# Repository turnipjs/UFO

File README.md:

# UFO

This is the Unified Full-size Ortholinear keyboard, or UFO for short. It has 114 keys in 6 rows and 19 columns, per key RGB, and N-Key roll over. It is built around a Raspberry Pi Pico and has a doodle of a UFO abducting a spherical cow in a vacuum.

# BOM
1x Main PCB  
1x Bottom Case PCB  
1x Top Plate PCB  
1x Raspberry Pi Pico  
114x Kailh style hot swap sockets for MX style switches  
114x SK6812-MINI-E RGB LEDs  
114x 1N4148W or other similar SOD-123 diodes  
Solder, Solder Paste, Flux as needed  
8x M2 threaded 3mm diameter 8mm long standoffs  
8x M2 threaded 5mm long screws  

# Firmware
The firmware will be available as the UFO keyboard in QMK repository. It is also available in [my personal QMK repository](https://github.com/turnipjs/qmk_firmware).

# Images

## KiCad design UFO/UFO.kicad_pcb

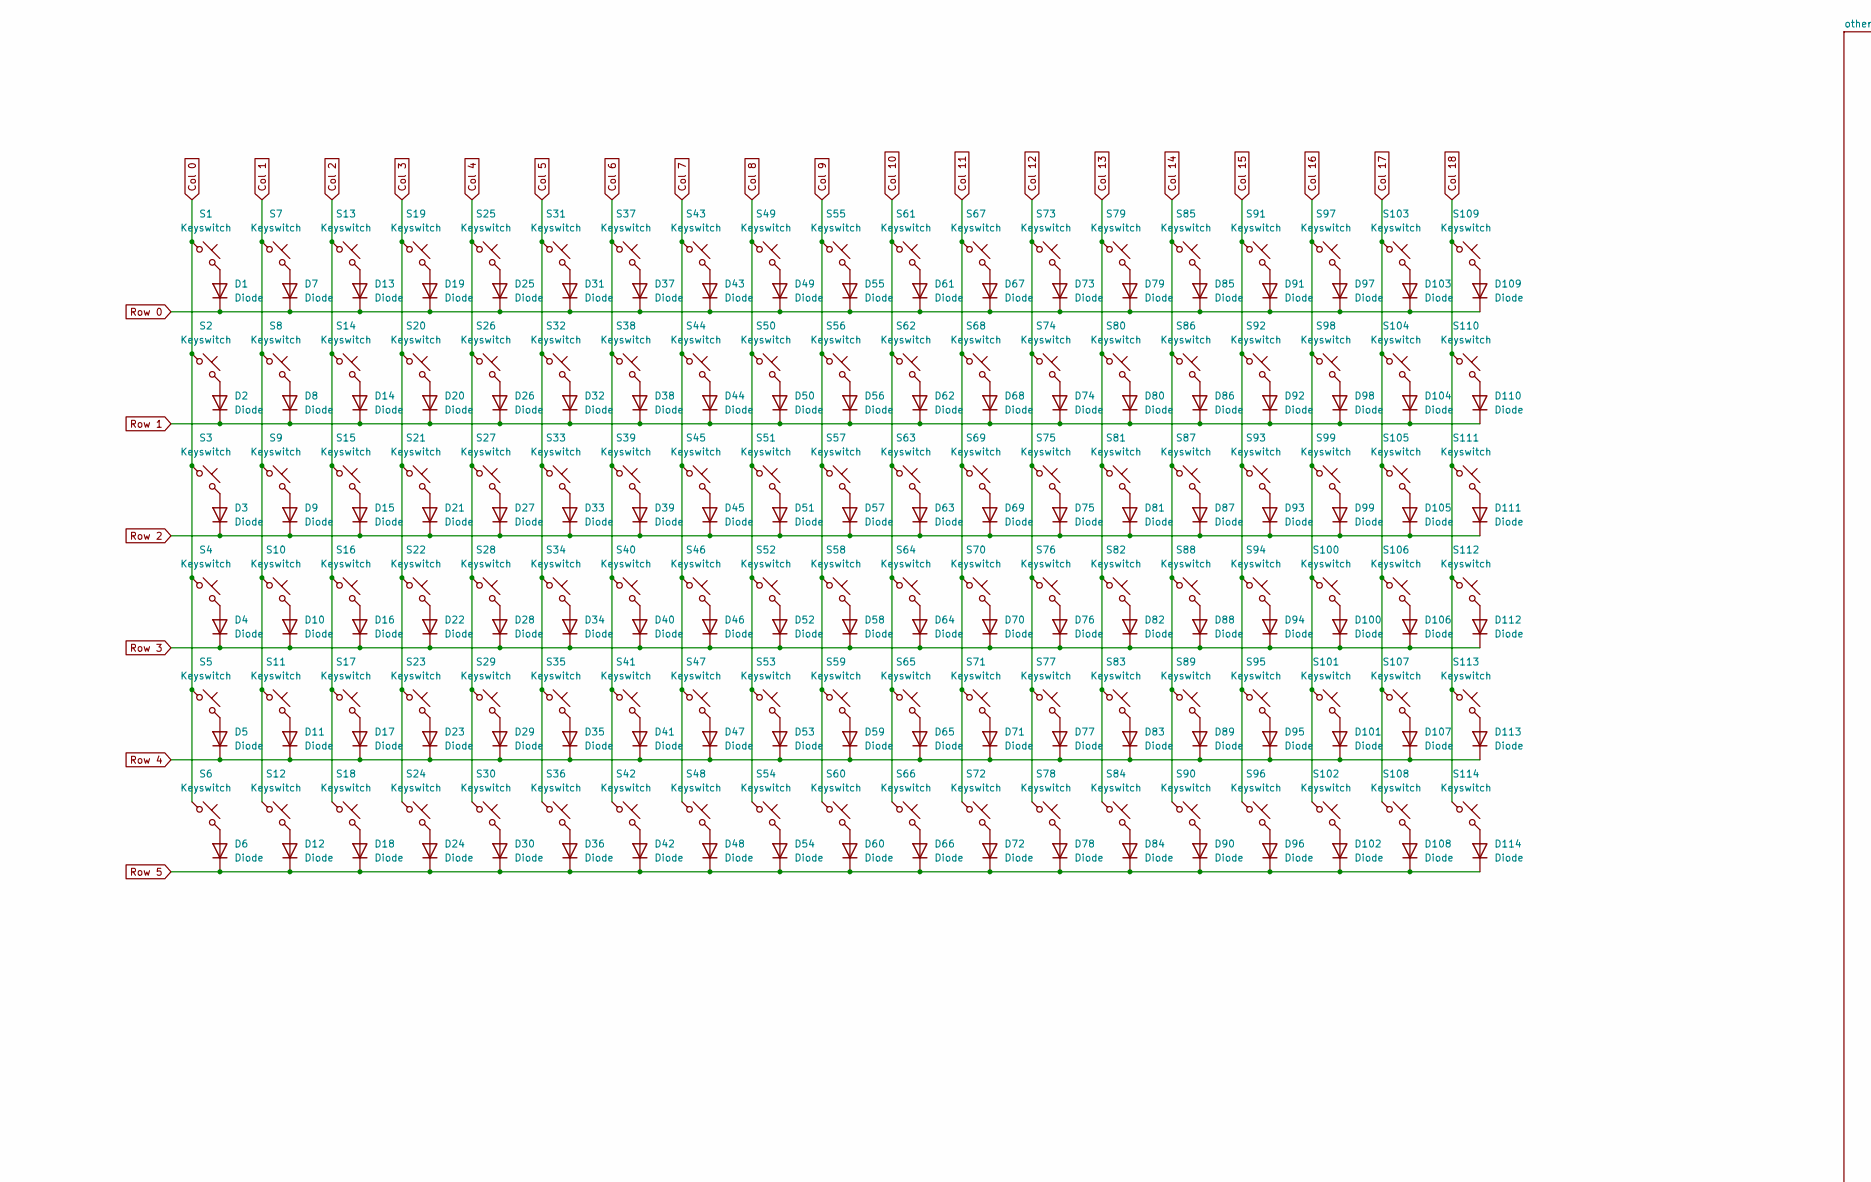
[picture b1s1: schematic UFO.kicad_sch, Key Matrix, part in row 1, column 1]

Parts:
D1, D2, D3, D4, D5, D6, D7, D8, D9, D10, D11, D12, D13, D14, D15, D16, D17, D18, D19, D20, D21, D22, D23, D24, D25, D26, D27, D28, D29, D30, D31, D32, D33, D34, D35, D36, D37, D38, D39, D40, D41, D42, D43, D44, D45, D46, D47, D48, D49, D50, D51, D52, D53, D54, D55, D56, D57, D58, D59, D60, D61, D62, D63, D64, D65, D66, D67, D68, D69, D70, D71, D72, D73, D74, D75, D76, D77, D78, D79, D80, D81, D82, D83, D84, D85, D86, D87, D88, D89, D90, D91, D92, D93, D94, D95, D96, D97, D98, D99, D100, D101, D102, D103, D104, D105, D106, D107, D108, D109, D110, D111, D112, D113, D114: Diode; Diode_SOD-123
S1, S2, S3, S4, S5, S6, S7, S8, S9, S10, S11, S12, S13, S14, S15, S16, S17, S18, S19, S20, S21, S22, S23, S24, S25, S26, S27, S28, S29, S30, S31, S32, S33, S34, S35, S36, S37, S38, S39, S40, S41, S42, S43, S44, S45, S46, S47, S48, S49, S50, S51, S52, S53, S54, S55, S56, S57, S58, S59, S60, S61, S62, S63, S64, S65, S66, S67, S68, S69, S70, S71, S72, S73, S74, S75, S76, S77, S78, S79, S80, S81, S82, S83, S84, S85, S86, S87, S88, S89, S90, S91, S92, S93, S94, S95, S96, S97, S98, S99, S100, S101, S102, S103, S104, S105, S106, S107, S108, S109, S110, S111, S112, S113, S114: Keyswitch; Hotswap_MX_1.00u

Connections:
Col 0: S1.1, S2.1, S3.1, S4.1, S5.1, S6.1; also elsewhere on the board
Col 1: S7.1, S8.1, S9.1, S10.1, S11.1, S12.1; also elsewhere on the board
Col 2: S13.1, S14.1, S15.1, S16.1, S17.1, S18.1; also elsewhere on the board
Col 3: S19.1, S20.1, S21.1, S22.1, S23.1, S24.1; also elsewhere on the board
Col 4: S25.1, S26.1, S27.1, S28.1, S29.1, S30.1; also elsewhere on the board
Col 5: S31.1, S32.1, S33.1, S34.1, S35.1, S36.1; also elsewhere on the board
Col 6: S37.1, S38.1, S39.1, S40.1, S41.1, S42.1; also elsewhere on the board
Col 7: S43.1, S44.1, S45.1, S46.1, S47.1, S48.1; also elsewhere on the board
Col 8: S49.1, S50.1, S51.1, S52.1, S53.1, S54.1; also elsewhere on the board
Col 9: S55.1, S56.1, S57.1, S58.1, S59.1, S60.1; also elsewhere on the board
Col 10: S61.1, S62.1, S63.1, S64.1, S65.1, S66.1; also elsewhere on the board
Col 11: S67.1, S68.1, S69.1, S70.1, S71.1, S72.1; also elsewhere on the board
Col 12: S73.1, S74.1, S75.1, S76.1, S77.1, S78.1; also elsewhere on the board
Col 13: S79.1, S80.1, S81.1, S82.1, S83.1, S84.1; also elsewhere on the board
Col 14: S85.1, S86.1, S87.1, S88.1, S89.1, S90.1; also elsewhere on the board
Col 15: S91.1, S92.1, S93.1, S94.1, S95.1, S96.1; also elsewhere on the board
Col 16: S97.1, S98.1, S99.1, S100.1, S101.1, S102.1; also elsewhere on the board
Col 17: S103.1, S104.1, S105.1, S106.1, S107.1, S108.1; also elsewhere on the board
Col 18: S109.1, S110.1, S111.1, S112.1, S113.1, S114.1; also elsewhere on the board
unnamed: D1.2 (A), S1.2
unnamed: D2.2 (A), S2.2
unnamed: D3.2 (A), S3.2
unnamed: D4.2 (A), S4.2
unnamed: D5.2 (A), S5.2
unnamed: D6.2 (A), S6.2
unnamed: D7.2 (A), S7.2
unnamed: D8.2 (A), S8.2
unnamed: D9.2 (A), S9.2
unnamed: D10.2 (A), S10.2
unnamed: D11.2 (A), S11.2
unnamed: D12.2 (A), S12.2
unnamed: D13.2 (A), S13.2
unnamed: D14.2 (A), S14.2
unnamed: D15.2 (A), S15.2
unnamed: D16.2 (A), S16.2
unnamed: D17.2 (A), S17.2
unnamed: D18.2 (A), S18.2
unnamed: D19.2 (A), S19.2
unnamed: D20.2 (A), S20.2
unnamed: D21.2 (A), S21.2
unnamed: D22.2 (A), S22.2
unnamed: D23.2 (A), S23.2
unnamed: D24.2 (A), S24.2
unnamed: D25.2 (A), S25.2
unnamed: D26.2 (A), S26.2
unnamed: D27.2 (A), S27.2
unnamed: D28.2 (A), S28.2
unnamed: D29.2 (A), S29.2
unnamed: D30.2 (A), S30.2
unnamed: D31.2 (A), S31.2
unnamed: D32.2 (A), S32.2
unnamed: D33.2 (A), S33.2
unnamed: D34.2 (A), S34.2
unnamed: D35.2 (A), S35.2
unnamed: D36.2 (A), S36.2
unnamed: D37.2 (A), S37.2
unnamed: D38.2 (A), S38.2
unnamed: D39.2 (A), S39.2
unnamed: D40.2 (A), S40.2
unnamed: D41.2 (A), S41.2
unnamed: D42.2 (A), S42.2
unnamed: D43.2 (A), S43.2
unnamed: D44.2 (A), S44.2
unnamed: D45.2 (A), S45.2
unnamed: D46.2 (A), S46.2
unnamed: D47.2 (A), S47.2
unnamed: D48.2 (A), S48.2
unnamed: D49.2 (A), S49.2
unnamed: D50.2 (A), S50.2
unnamed: D51.2 (A), S51.2
unnamed: D52.2 (A), S52.2
unnamed: D53.2 (A), S53.2
unnamed: D54.2 (A), S54.2
unnamed: D55.2 (A), S55.2
unnamed: D56.2 (A), S56.2
unnamed: D57.2 (A), S57.2
unnamed: D58.2 (A), S58.2
unnamed: D59.2 (A), S59.2
unnamed: D60.2 (A), S60.2
unnamed: D61.2 (A), S61.2
unnamed: D62.2 (A), S62.2
unnamed: D63.2 (A), S63.2
unnamed: D64.2 (A), S64.2
unnamed: D65.2 (A), S65.2
unnamed: D66.2 (A), S66.2
unnamed: D67.2 (A), S67.2
unnamed: D68.2 (A), S68.2
unnamed: D69.2 (A), S69.2
unnamed: D70.2 (A), S70.2
unnamed: D71.2 (A), S71.2
unnamed: D72.2 (A), S72.2
unnamed: D73.2 (A), S73.2
unnamed: D74.2 (A), S74.2
unnamed: D75.2 (A), S75.2
unnamed: D76.2 (A), S76.2
unnamed: D77.2 (A), S77.2
unnamed: D78.2 (A), S78.2
unnamed: D79.2 (A), S79.2
unnamed: D80.2 (A), S80.2
unnamed: D81.2 (A), S81.2
unnamed: D82.2 (A), S82.2
unnamed: D83.2 (A), S83.2
unnamed: D84.2 (A), S84.2
unnamed: D85.2 (A), S85.2
unnamed: D86.2 (A), S86.2
unnamed: D87.2 (A), S87.2
unnamed: D88.2 (A), S88.2
unnamed: D89.2 (A), S89.2
unnamed: D90.2 (A), S90.2
unnamed: D91.2 (A), S91.2
unnamed: D92.2 (A), S92.2
unnamed: D93.2 (A), S93.2
unnamed: D94.2 (A), S94.2
unnamed: D95.2 (A), S95.2
unnamed: D96.2 (A), S96.2
unnamed: D97.2 (A), S97.2
unnamed: D98.2 (A), S98.2
unnamed: D99.2 (A), S99.2
unnamed: D100.2 (A), S100.2
unnamed: D101.2 (A), S101.2
unnamed: D102.2 (A), S102.2
unnamed: D103.2 (A), S103.2
unnamed: D104.2 (A), S104.2
unnamed: D105.2 (A), S105.2
unnamed: D106.2 (A), S106.2
unnamed: D107.2 (A), S107.2
unnamed: D108.2 (A), S108.2
unnamed: D109.2 (A), S109.2
unnamed: D110.2 (A), S110.2
unnamed: D111.2 (A), S111.2
unnamed: D112.2 (A), S112.2
unnamed: D113.2 (A), S113.2
unnamed: D114.2 (A), S114.2
Row 0: D1.1 (K), D7.1 (K), D13.1 (K), D19.1 (K), D25.1 (K), D31.1 (K), D37.1 (K), D43.1 (K), D49.1 (K), D55.1 (K), D61.1 (K), D67.1 (K), D73.1 (K), D79.1 (K), D85.1 (K), D91.1 (K), D97.1 (K), D103.1 (K), D109.1 (K); also elsewhere on the board
Row 1: D2.1 (K), D8.1 (K), D14.1 (K), D20.1 (K), D26.1 (K), D32.1 (K), D38.1 (K), D44.1 (K), D50.1 (K), D56.1 (K), D62.1 (K), D68.1 (K), D74.1 (K), D80.1 (K), D86.1 (K), D92.1 (K), D98.1 (K), D104.1 (K), D110.1 (K); also elsewhere on the board
Row 2: D3.1 (K), D9.1 (K), D15.1 (K), D21.1 (K), D27.1 (K), D33.1 (K), D39.1 (K), D45.1 (K), D51.1 (K), D57.1 (K), D63.1 (K), D69.1 (K), D75.1 (K), D81.1 (K), D87.1 (K), D93.1 (K), D99.1 (K), D105.1 (K), D111.1 (K); also elsewhere on the board
Row 3: D4.1 (K), D10.1 (K), D16.1 (K), D22.1 (K), D28.1 (K), D34.1 (K), D40.1 (K), D46.1 (K), D52.1 (K), D58.1 (K), D64.1 (K), D70.1 (K), D76.1 (K), D82.1 (K), D88.1 (K), D94.1 (K), D100.1 (K), D106.1 (K), D112.1 (K); also elsewhere on the board
Row 4: D5.1 (K), D11.1 (K), D17.1 (K), D23.1 (K), D29.1 (K), D35.1 (K), D41.1 (K), D47.1 (K), D53.1 (K), D59.1 (K), D65.1 (K), D71.1 (K), D77.1 (K), D83.1 (K), D89.1 (K), D95.1 (K), D101.1 (K), D107.1 (K), D113.1 (K); also elsewhere on the board
Row 5: D6.1 (K), D12.1 (K), D18.1 (K), D24.1 (K), D30.1 (K), D36.1 (K), D42.1 (K), D48.1 (K), D54.1 (K), D60.1 (K), D66.1 (K), D72.1 (K), D78.1 (K), D84.1 (K), D90.1 (K), D96.1 (K), D102.1 (K), D108.1 (K), D114.1 (K); also elsewhere on the board

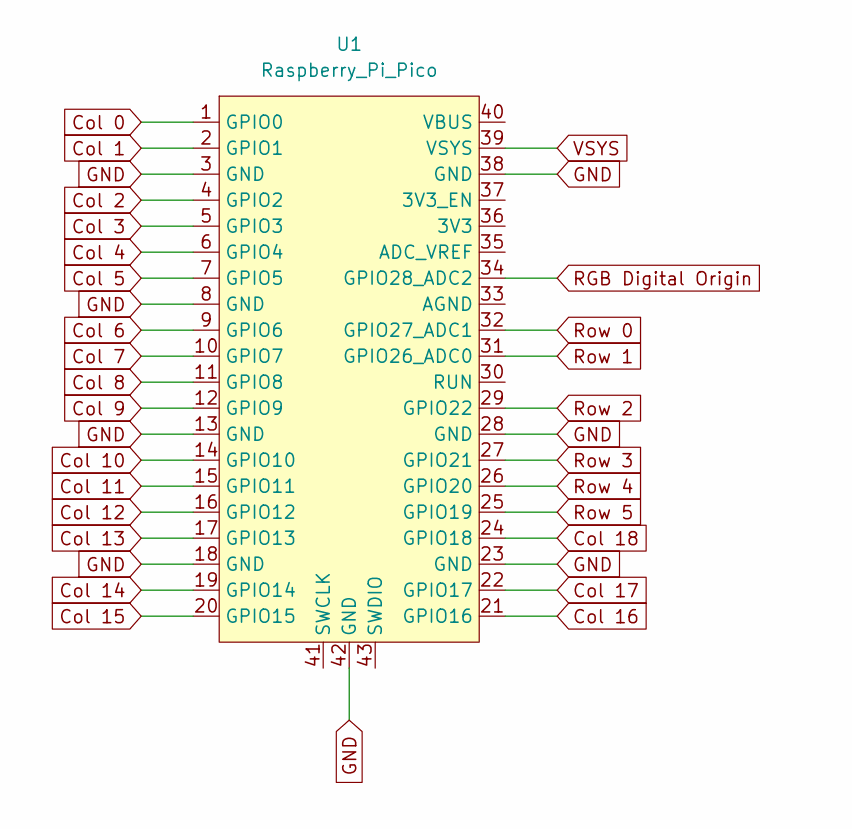
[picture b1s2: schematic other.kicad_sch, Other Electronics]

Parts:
U1: Raspberry_Pi_Pico

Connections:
Col 0: U1.1 (GPIO0); also elsewhere on the board
Col 1: U1.2 (GPIO1); also elsewhere on the board
Col 2: U1.4 (GPIO2); also elsewhere on the board
Col 3: U1.5 (GPIO3); also elsewhere on the board
Col 4: U1.6 (GPIO4); also elsewhere on the board
Col 5: U1.7 (GPIO5); also elsewhere on the board
Col 6: U1.9 (GPIO6); also elsewhere on the board
Col 7: U1.10 (GPIO7); also elsewhere on the board
Col 8: U1.11 (GPIO8); also elsewhere on the board
Col 9: U1.12 (GPIO9); also elsewhere on the board
Col 10: U1.14 (GPIO10); also elsewhere on the board
Col 11: U1.15 (GPIO11); also elsewhere on the board
Col 12: U1.16 (GPIO12); also elsewhere on the board
Col 13: U1.17 (GPIO13); also elsewhere on the board
Col 14: U1.19 (GPIO14); also elsewhere on the board
Col 15: U1.20 (GPIO15); also elsewhere on the board
Col 16: U1.21 (GPIO16); also elsewhere on the board
Col 17: U1.22 (GPIO17); also elsewhere on the board
Col 18: U1.24 (GPIO18); also elsewhere on the board
GND: U1.3 (GND), U1.8 (GND), U1.13 (GND), U1.18 (GND), U1.23 (GND), U1.28 (GND), U1.38 (GND), U1.42 (GND); also elsewhere on the board
RGB Digital Origin: U1.34 (GPIO28_ADC2); also elsewhere on the board
Row 0: U1.32 (GPIO27_ADC1); also elsewhere on the board
Row 1: U1.31 (GPIO26_ADC0); also elsewhere on the board
Row 2: U1.29 (GPIO22); also elsewhere on the board
Row 3: U1.27 (GPIO21); also elsewhere on the board
Row 4: U1.26 (GPIO20); also elsewhere on the board
Row 5: U1.25 (GPIO19); also elsewhere on the board
VSYS: U1.39 (VSYS); also elsewhere on the board

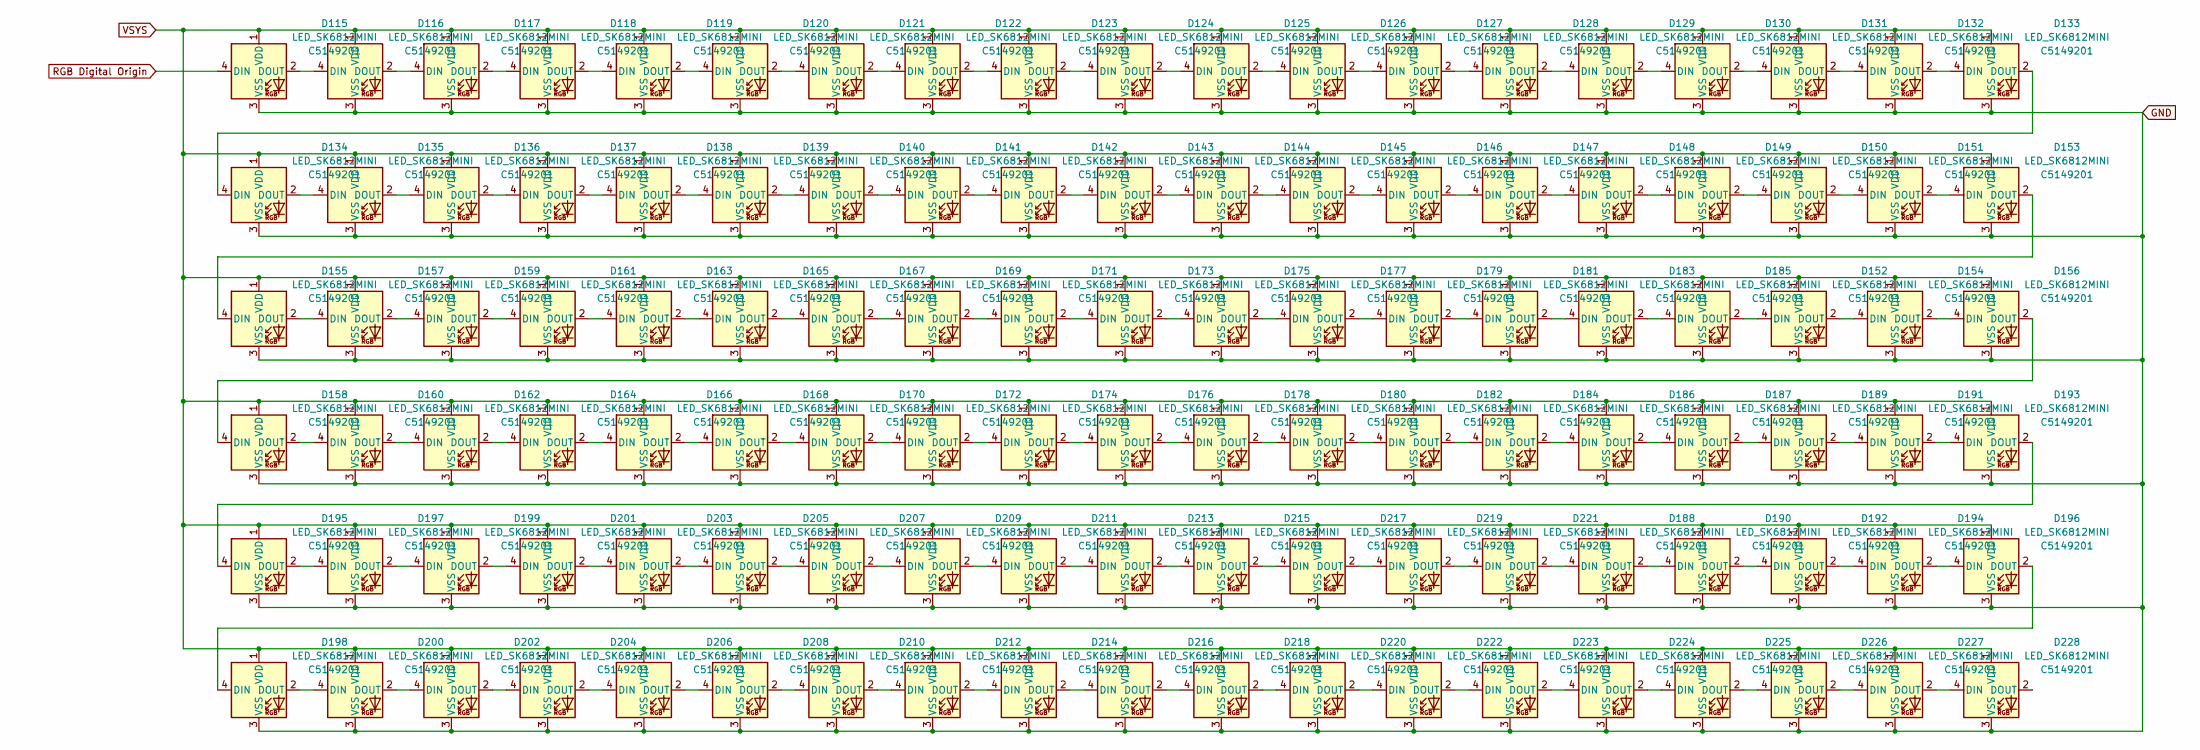
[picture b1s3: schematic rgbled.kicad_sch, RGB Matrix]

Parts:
D115, D116, D117, D118, D119, D120, D121, D122, D123, D124, D125, D126, D127, D128, D129, D130, D131, D132, D133, D134, D135, D136, D137, D138, D139, D140, D141, D142, D143, D144, D145, D146, D147, D148, D149, D150, D151, D152, D153, D154, D155, D156, D157, D158, D159, D160, D161, D162, D163, D164, D165, D166, D167, D168, D169, D170, D171, D172, D173, D174, D175, D176, D177, D178, D179, D180, D181, D182, D183, D184, D185, D186, D187, D188, D189, D190, D191, D192, D193, D194, D195, D196, D197, D198, D199, D200, D201, D202, D203, D204, D205, D206, D207, D208, D209, D210, D211, D212, D213, D214, D215, D216, D217, D218, D219, D220, D221, D222, D223, D224, D225, D226, D227, D228: LED_SK6812MINI; LCSC C5149201

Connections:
GND: D115.3 (VSS), D116.3 (VSS), D117.3 (VSS), D118.3 (VSS), D119.3 (VSS), D120.3 (VSS), D121.3 (VSS), D122.3 (VSS), D123.3 (VSS), D124.3 (VSS), D125.3 (VSS), D126.3 (VSS), D127.3 (VSS), D128.3 (VSS), D129.3 (VSS), D130.3 (VSS), D131.3 (VSS), D132.3 (VSS), D133.3 (VSS), D134.3 (VSS), D135.3 (VSS), D136.3 (VSS), D137.3 (VSS), D138.3 (VSS), D139.3 (VSS), D140.3 (VSS), D141.3 (VSS), D142.3 (VSS), D143.3 (VSS), D144.3 (VSS), D145.3 (VSS), D146.3 (VSS), D147.3 (VSS), D148.3 (VSS), D149.3 (VSS), D150.3 (VSS), D151.3 (VSS), D152.3 (VSS), D153.3 (VSS), D154.3 (VSS), D155.3 (VSS), D156.3 (VSS), D157.3 (VSS), D158.3 (VSS), D159.3 (VSS), D160.3 (VSS), D161.3 (VSS), D162.3 (VSS), D163.3 (VSS), D164.3 (VSS), D165.3 (VSS), D166.3 (VSS), D167.3 (VSS), D168.3 (VSS), D169.3 (VSS), D170.3 (VSS), D171.3 (VSS), D172.3 (VSS), D173.3 (VSS), D174.3 (VSS), D175.3 (VSS), D176.3 (VSS), D177.3 (VSS), D178.3 (VSS), D179.3 (VSS), D180.3 (VSS), D181.3 (VSS), D182.3 (VSS), D183.3 (VSS), D184.3 (VSS), D185.3 (VSS), D186.3 (VSS), D187.3 (VSS), D188.3 (VSS), D189.3 (VSS), D190.3 (VSS), D191.3 (VSS), D192.3 (VSS), D193.3 (VSS), D194.3 (VSS), D195.3 (VSS), D196.3 (VSS), D197.3 (VSS), D198.3 (VSS), D199.3 (VSS), D200.3 (VSS), D201.3 (VSS), D202.3 (VSS), D203.3 (VSS), D204.3 (VSS), D205.3 (VSS), D206.3 (VSS), D207.3 (VSS), D208.3 (VSS), D209.3 (VSS), D210.3 (VSS), D211.3 (VSS), D212.3 (VSS), D213.3 (VSS), D214.3 (VSS), D215.3 (VSS), D216.3 (VSS), D217.3 (VSS), D218.3 (VSS), D219.3 (VSS), D220.3 (VSS), D221.3 (VSS), D222.3 (VSS), D223.3 (VSS), D224.3 (VSS), D225.3 (VSS), D226.3 (VSS), D227.3 (VSS), D228.3 (VSS); also elsewhere on the board
unnamed: D115.2 (DOUT), D116.4 (DIN)
unnamed: D116.2 (DOUT), D117.4 (DIN)
unnamed: D117.2 (DOUT), D118.4 (DIN)
unnamed: D118.2 (DOUT), D119.4 (DIN)
unnamed: D119.2 (DOUT), D120.4 (DIN)
unnamed: D120.2 (DOUT), D121.4 (DIN)
unnamed: D121.2 (DOUT), D122.4 (DIN)
unnamed: D122.2 (DOUT), D123.4 (DIN)
unnamed: D123.2 (DOUT), D124.4 (DIN)
unnamed: D124.2 (DOUT), D125.4 (DIN)
unnamed: D125.2 (DOUT), D126.4 (DIN)
unnamed: D126.2 (DOUT), D127.4 (DIN)
unnamed: D127.2 (DOUT), D128.4 (DIN)
unnamed: D128.2 (DOUT), D129.4 (DIN)
unnamed: D129.2 (DOUT), D130.4 (DIN)
unnamed: D130.2 (DOUT), D131.4 (DIN)
unnamed: D131.2 (DOUT), D132.4 (DIN)
unnamed: D132.2 (DOUT), D133.4 (DIN)
unnamed: D133.2 (DOUT), D134.4 (DIN)
unnamed: D134.2 (DOUT), D135.4 (DIN)
unnamed: D135.2 (DOUT), D136.4 (DIN)
unnamed: D136.2 (DOUT), D137.4 (DIN)
unnamed: D137.2 (DOUT), D138.4 (DIN)
unnamed: D138.2 (DOUT), D139.4 (DIN)
unnamed: D139.2 (DOUT), D140.4 (DIN)
unnamed: D140.2 (DOUT), D141.4 (DIN)
unnamed: D141.2 (DOUT), D142.4 (DIN)
unnamed: D142.2 (DOUT), D143.4 (DIN)
unnamed: D143.2 (DOUT), D144.4 (DIN)
unnamed: D144.2 (DOUT), D145.4 (DIN)
unnamed: D145.2 (DOUT), D146.4 (DIN)
unnamed: D146.2 (DOUT), D147.4 (DIN)
unnamed: D147.2 (DOUT), D148.4 (DIN)
unnamed: D148.2 (DOUT), D149.4 (DIN)
unnamed: D149.2 (DOUT), D150.4 (DIN)
unnamed: D150.2 (DOUT), D151.4 (DIN)
unnamed: D151.2 (DOUT), D153.4 (DIN)
unnamed: D152.4 (DIN), D185.2 (DOUT)
unnamed: D152.2 (DOUT), D154.4 (DIN)
unnamed: D153.2 (DOUT), D155.4 (DIN)
unnamed: D154.2 (DOUT), D156.4 (DIN)
unnamed: D155.2 (DOUT), D157.4 (DIN)
unnamed: D156.2 (DOUT), D158.4 (DIN)
unnamed: D157.2 (DOUT), D159.4 (DIN)
unnamed: D158.2 (DOUT), D160.4 (DIN)
unnamed: D159.2 (DOUT), D161.4 (DIN)
unnamed: D160.2 (DOUT), D162.4 (DIN)
unnamed: D161.2 (DOUT), D163.4 (DIN)
unnamed: D162.2 (DOUT), D164.4 (DIN)
unnamed: D163.2 (DOUT), D165.4 (DIN)
unnamed: D164.2 (DOUT), D166.4 (DIN)
unnamed: D165.2 (DOUT), D167.4 (DIN)
unnamed: D166.2 (DOUT), D168.4 (DIN)
unnamed: D167.2 (DOUT), D169.4 (DIN)
unnamed: D168.2 (DOUT), D170.4 (DIN)
unnamed: D169.2 (DOUT), D171.4 (DIN)
unnamed: D170.2 (DOUT), D172.4 (DIN)
unnamed: D171.2 (DOUT), D173.4 (DIN)
unnamed: D172.2 (DOUT), D174.4 (DIN)
unnamed: D173.2 (DOUT), D175.4 (DIN)
unnamed: D174.2 (DOUT), D176.4 (DIN)
unnamed: D175.2 (DOUT), D177.4 (DIN)
unnamed: D176.2 (DOUT), D178.4 (DIN)
unnamed: D177.2 (DOUT), D179.4 (DIN)
unnamed: D178.2 (DOUT), D180.4 (DIN)
unnamed: D179.2 (DOUT), D181.4 (DIN)
unnamed: D180.2 (DOUT), D182.4 (DIN)
unnamed: D181.2 (DOUT), D183.4 (DIN)
unnamed: D182.2 (DOUT), D184.4 (DIN)
unnamed: D183.2 (DOUT), D185.4 (DIN)
unnamed: D184.2 (DOUT), D186.4 (DIN)
unnamed: D186.2 (DOUT), D187.4 (DIN)
unnamed: D187.2 (DOUT), D189.4 (DIN)
unnamed: D188.4 (DIN), D221.2 (DOUT)
unnamed: D188.2 (DOUT), D190.4 (DIN)
unnamed: D189.2 (DOUT), D191.4 (DIN)
unnamed: D190.2 (DOUT), D192.4 (DIN)
unnamed: D191.2 (DOUT), D193.4 (DIN)
unnamed: D192.2 (DOUT), D194.4 (DIN)
unnamed: D193.2 (DOUT), D195.4 (DIN)
unnamed: D194.2 (DOUT), D196.4 (DIN)
unnamed: D195.2 (DOUT), D197.4 (DIN)
unnamed: D196.2 (DOUT), D198.4 (DIN)
unnamed: D197.2 (DOUT), D199.4 (DIN)
unnamed: D198.2 (DOUT), D200.4 (DIN)
unnamed: D199.2 (DOUT), D201.4 (DIN)
unnamed: D200.2 (DOUT), D202.4 (DIN)
unnamed: D201.2 (DOUT), D203.4 (DIN)
unnamed: D202.2 (DOUT), D204.4 (DIN)
unnamed: D203.2 (DOUT), D205.4 (DIN)
unnamed: D204.2 (DOUT), D206.4 (DIN)
unnamed: D205.2 (DOUT), D207.4 (DIN)
unnamed: D206.2 (DOUT), D208.4 (DIN)
unnamed: D207.2 (DOUT), D209.4 (DIN)
unnamed: D208.2 (DOUT), D210.4 (DIN)
unnamed: D209.2 (DOUT), D211.4 (DIN)
unnamed: D210.2 (DOUT), D212.4 (DIN)
unnamed: D211.2 (DOUT), D213.4 (DIN)
unnamed: D212.2 (DOUT), D214.4 (DIN)
unnamed: D213.2 (DOUT), D215.4 (DIN)
unnamed: D214.2 (DOUT), D216.4 (DIN)
unnamed: D215.2 (DOUT), D217.4 (DIN)
unnamed: D216.2 (DOUT), D218.4 (DIN)
unnamed: D217.2 (DOUT), D219.4 (DIN)
unnamed: D218.2 (DOUT), D220.4 (DIN)
unnamed: D219.2 (DOUT), D221.4 (DIN)
unnamed: D220.2 (DOUT), D222.4 (DIN)
unnamed: D222.2 (DOUT), D223.4 (DIN)
unnamed: D223.2 (DOUT), D224.4 (DIN)
unnamed: D224.2 (DOUT), D225.4 (DIN)
unnamed: D225.2 (DOUT), D226.4 (DIN)
unnamed: D226.2 (DOUT), D227.4 (DIN)
unnamed: D227.2 (DOUT), D228.4 (DIN)
RGB Digital Origin: D115.4 (DIN); also elsewhere on the board
VSYS: D115.1 (VDD), D116.1 (VDD), D117.1 (VDD), D118.1 (VDD), D119.1 (VDD), D120.1 (VDD), D121.1 (VDD), D122.1 (VDD), D123.1 (VDD), D124.1 (VDD), D125.1 (VDD), D126.1 (VDD), D127.1 (VDD), D128.1 (VDD), D129.1 (VDD), D130.1 (VDD), D131.1 (VDD), D132.1 (VDD), D133.1 (VDD), D134.1 (VDD), D135.1 (VDD), D136.1 (VDD), D137.1 (VDD), D138.1 (VDD), D139.1 (VDD), D140.1 (VDD), D141.1 (VDD), D142.1 (VDD), D143.1 (VDD), D144.1 (VDD), D145.1 (VDD), D146.1 (VDD), D147.1 (VDD), D148.1 (VDD), D149.1 (VDD), D150.1 (VDD), D151.1 (VDD), D152.1 (VDD), D153.1 (VDD), D154.1 (VDD), D155.1 (VDD), D156.1 (VDD), D157.1 (VDD), D158.1 (VDD), D159.1 (VDD), D160.1 (VDD), D161.1 (VDD), D162.1 (VDD), D163.1 (VDD), D164.1 (VDD), D165.1 (VDD), D166.1 (VDD), D167.1 (VDD), D168.1 (VDD), D169.1 (VDD), D170.1 (VDD), D171.1 (VDD), D172.1 (VDD), D173.1 (VDD), D174.1 (VDD), D175.1 (VDD), D176.1 (VDD), D177.1 (VDD), D178.1 (VDD), D179.1 (VDD), D180.1 (VDD), D181.1 (VDD), D182.1 (VDD), D183.1 (VDD), D184.1 (VDD), D185.1 (VDD), D186.1 (VDD), D187.1 (VDD), D188.1 (VDD), D189.1 (VDD), D190.1 (VDD), D191.1 (VDD), D192.1 (VDD), D193.1 (VDD), D194.1 (VDD), D195.1 (VDD), D196.1 (VDD), D197.1 (VDD), D198.1 (VDD), D199.1 (VDD), D200.1 (VDD), D201.1 (VDD), D202.1 (VDD), D203.1 (VDD), D204.1 (VDD), D205.1 (VDD), D206.1 (VDD), D207.1 (VDD), D208.1 (VDD), D209.1 (VDD), D210.1 (VDD), D211.1 (VDD), D212.1 (VDD), D213.1 (VDD), D214.1 (VDD), D215.1 (VDD), D216.1 (VDD), D217.1 (VDD), D218.1 (VDD), D219.1 (VDD), D220.1 (VDD), D221.1 (VDD), D222.1 (VDD), D223.1 (VDD), D224.1 (VDD), D225.1 (VDD), D226.1 (VDD), D227.1 (VDD), D228.1 (VDD); also elsewhere on the board

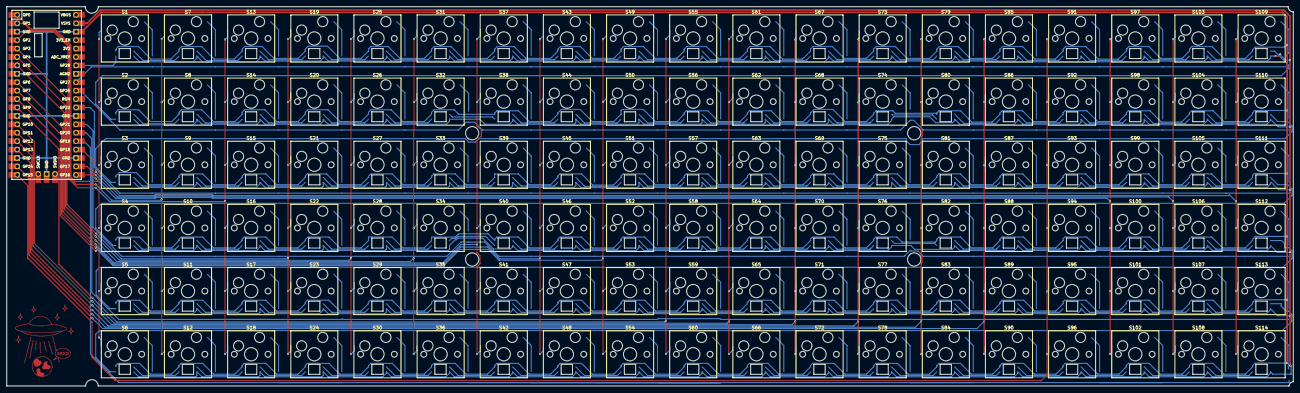
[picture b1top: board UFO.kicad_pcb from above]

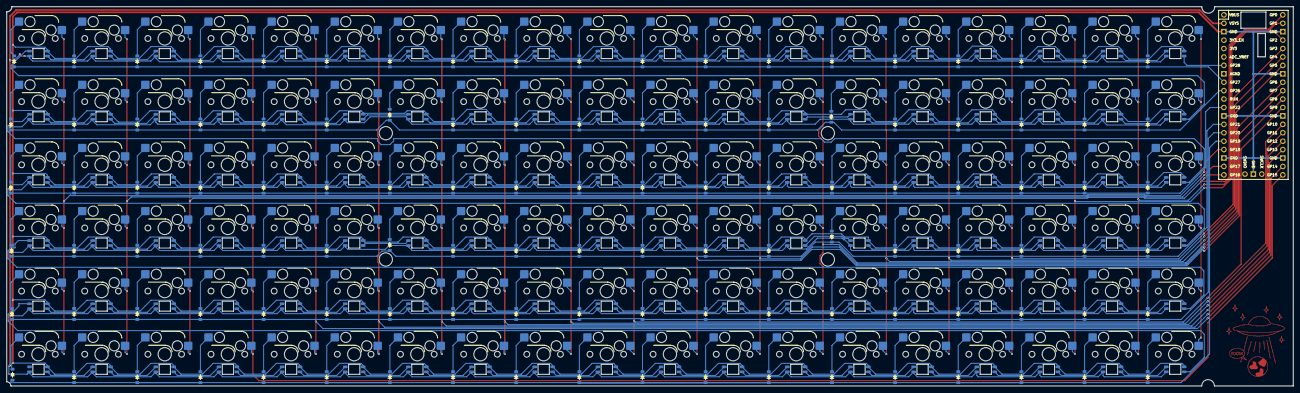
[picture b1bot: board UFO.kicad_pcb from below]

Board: 2 copper layers, 388.1 x 114.4 mm, 343 parts (228 on the bottom side), 255 nets.

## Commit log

2025-09-17 ufo v1.1 with case (the version that I had made)
